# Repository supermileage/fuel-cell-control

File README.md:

# Fuel-Cell-Control
Fuel Cell Control Stuff

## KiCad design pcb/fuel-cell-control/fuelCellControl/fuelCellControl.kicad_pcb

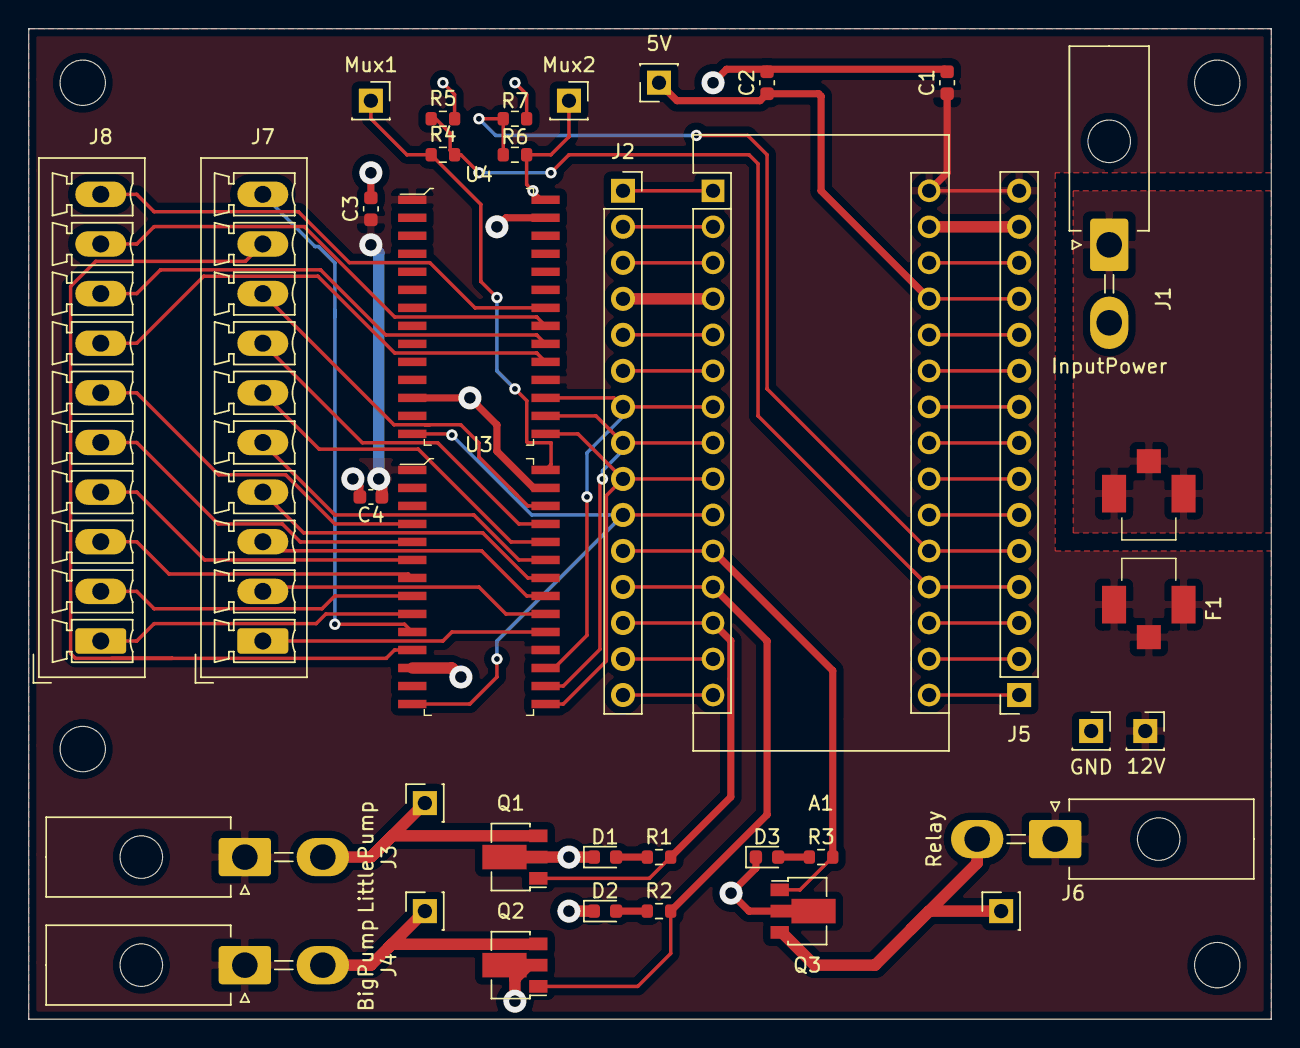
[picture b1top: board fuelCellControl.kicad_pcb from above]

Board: 2 copper layers, 87.6 x 69.9 mm, 41 parts (0 on the bottom side), 58 nets.

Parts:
A1: Arduino_Nano_Every; Arduino_Nano
C1, C2: 1uF; C_0603_1608Metric
C3, C4: 0.1uF; C_0603_1608Metric
D1, D2, D3: LED; LED_0603_1608Metric
F1: Fuse; 3586KTR
H1, H2, H3, H4: MountingHole; MountingHole_3.2mm_M3
J1: InputPower; Molex_Mini-Fit_Jr_5569-02A2_2x01_P4.20mm_Horizontal
J2, J5: Conn_01x15_Female; PinSocket_1x15_P2.54mm_Vertical
J3: LittlePump; Molex_Mini-Fit_Jr_5569-02A2_2x01_P4.20mm_Horizontal
J4: BigPump; Molex_Mini-Fit_Jr_5569-02A2_2x01_P4.20mm_Horizontal
J6: Relay; Molex_Mini-Fit_Jr_5569-02A2_2x01_P4.20mm_Horizontal
J7, J8: Conn_01x10_Male; PhoenixContact_MCV_1,5_10-G-3.5_1x10_P3.50mm_Vertical
Q1, Q2, Q3: Q_NMOS_GDS; SOT-89-3
R1, R2, R3: 1.5k; R_0603_1608Metric
R4, R6: 820k; R_0603_1608Metric
R5, R7: 430k; R_0603_1608Metric
TP1: LPump; PinSocket_1x01_P2.54mm_Vertical
TP2: BPump; PinSocket_1x01_P2.54mm_Vertical
TP3: 12V; PinSocket_1x01_P2.54mm_Vertical
TP4: GND; PinSocket_1x01_P2.54mm_Vertical
TP5: 5V; PinSocket_1x01_P2.54mm_Vertical
TP6: RelayT; PinSocket_1x01_P2.54mm_Vertical
TP7: Mux1; PinSocket_1x01_P2.54mm_Vertical
TP8: Mux2; PinSocket_1x01_P2.54mm_Vertical
U3, U4: MUX506IDWR; SOIC-28_W7.5mm

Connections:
+5V: A1.27, C2.1, J5.12, TP5.1
+12V: A1.30, C1.1, C3.1, C4.1, F1.1, J3.1, J4.1, J5.15, J6.1, TP3.1, U3.1, U3.18, U4.1, U4.18
/AREF: A1.18, J5.3
/Analog1: A1.20, J5.5, R6.2, R7.1
/Analog2: A1.21, J5.6
/Analog3: A1.22, J5.7
/Analog4_SDA: A1.23, J5.8
/Analog5_SCL: A1.24, J5.9
/Analog6: A1.25, J5.10
/Analog7: A1.26, J5.11
/BigPump: A1.12, J2.12, Q2.1, R2.2
/D2: A1.5, J2.5
/D3_PWM: A1.6, J2.6
/LittlePump: A1.13, J2.13, Q1.1, R1.2
/MISO: A1.15, J2.15
/MOSI: A1.14, J2.14
/MuxAnalog: A1.19, J5.4, R4.2, R5.1
/MuxSelect0: A1.7, J2.7, U3.17, U4.17
/MuxSelect1: A1.8, J2.8, U3.16, U4.16
/MuxSelect2: A1.9, J2.9, U3.15, U4.15
/MuxSelect3: A1.10, J2.10, U3.14, U4.14
/Nano3V3Out: A1.17, J5.2
/RESET1: A1.3, J2.3
/RESET2: A1.28, J5.13
/RX1: A1.2, J2.2
/Relay: A1.11, J2.11, Q3.1, R3.2
/SCK: A1.16, J5.1
/TX1: A1.1, J2.1
GND: A1.4, A1.29, C1.2, C2.2, C3.2, C4.2, D1.1, D2.1, D3.1, J1.2, J2.4, J5.14, Q1.2, Q2.2, Q3.2, R5.2, R7.2, TP4.1, U3.12, U3.27, U4.12, U4.27
unnamed: D1.2, R1.1
unnamed: D2.2, R2.1
unnamed: D3.2, R3.1
unnamed: F1.2, J1.1
unnamed: J3.2, Q1.3, TP1.1
unnamed: J4.2, Q2.3, TP2.1
unnamed: J6.2, Q3.3, TP6.1
unnamed: J7.1, U3.19
unnamed: J7.2, U3.20
unnamed: J7.3, U3.21
unnamed: J7.4, U3.22
unnamed: J7.5, U3.23
unnamed: J7.6, U3.24
unnamed: J7.7, U3.25
unnamed: J7.8, U3.26
unnamed: J7.9, U3.11
unnamed: J7.10, U3.10
unnamed: J8.1, U3.9
unnamed: J8.2, U3.8
unnamed: J8.3, U3.7
unnamed: J8.4, U3.6
unnamed: J8.5, U3.5
unnamed: J8.6, U3.4
unnamed: J8.7, U4.19
unnamed: J8.8, U4.20
unnamed: J8.9, U4.21
unnamed: J8.10, U4.22
unnamed: R4.1, TP7.1, U3.28
unnamed: R6.1, TP8.1, U4.28

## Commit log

2021-06-15 adds kicad project files
2021-06-18 Adds MUXes, DCDC Converter, and relevant libraries
2021-07-14 daq code
2021-07-14 firmware code
2021-07-17 suiicide
2021-07-19 updates firmware
2021-07-20 Adds just some small firmware tweaks
2021-07-21 Adds remote logging fw
2021-11-06 initial schematic
2021-11-14 initial pcb design
2021-11-20 enlarged power traces
2021-11-21 updated based on design review
2021-11-23 cleans up some longer traces
2021-11-27 remove voltage regulator and update connector spacing and tracing
2021-11-28 adds supermileage logo and updates part information
2021-12-18 rev1.0 schematic
2022-01-16 initial firmware
2022-01-30 first test
2022-02-12 update logic, fix bug in voltage reading
2022-02-15 update firmware with expected zero cells
2022-02-17 delay for mux switching and comments for changing mode in serial
2022-02-17 print error cells
2022-02-24 initial control test
2022-02-28 hardcode cell positions
2022-03-06 dyno test fixed all but highest cell
2022-03-06 special stop char
2022-03-10 works with some rewiring
2022-03-11 updates to stop if stuck in init and includes cell lookup table
2022-03-12 serial switch and mode switch guide
2022-03-24 changes I forgot to commit
2022-03-26 removes temp thing
2022-03-27 hydrogen sensor test and datasheets
2022-03-28 adds new analog pin readings
2022-03-29 modified telemetry
2022-03-29 calibration
2022-03-31 plot limit
2022-03-31 remove break
2022-03-31 makes cell numbers the actual cell numbers
2022-03-31 new analog
2022-04-09 Adds FCP layout schematic
2022-04-11 control for potential voltage spikes
2022-05-06 version used at SEMA 2022
2022-11-19 telemetry serial output
2022-11-19 fixes compiler errors
2022-11-19 updates for track day 2022
2022-11-26 track day updates
2023-03-04 19 cells
